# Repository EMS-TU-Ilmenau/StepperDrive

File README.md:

# StepperDrive
This embedded project features a simple controller board for a stepper motor. 
Multiple boards can be connected together. 
One of it has to be attached to USB and power supply. 
Each motor can then be controlled with simple SCPI-like commands via UART (8N1 9600baud) to move to a position, set the maximum rate and acceleration etc.

## Features
- Uses TMC2209 stepper driver IC for smooth and quiet operation
- Multiple boards can be connected to each other via ethernet-cables
- USB-C interface for control and flashing firmware

Note that there is no real anti-collision protocol, but as the communication is quit fast, there should be no problem to query each motors parameters individually with their IDs after another.
E.g. `AX1:POS?` then `AX2:POS?`.
Sending commands can be even done simultaneously, e.g. `AX1:POS 180;AX2:POS 22.5`.

## Flashing
The firmware is written in AVR-C for the ATtiny814. To start programming, an extended AVR toolchain is needed, which can be found in the Arduino IDE (the GNU AVR toolchain does NOT support the ATtiny814):
- Go to https://www.arduino.cc/en/software and scroll down to "legacy IDE (1.8.X)" and download the zipped version for your OS
- Unzip and add 
  - (Linux) *arduino-1.8.19-linux64.tar/arduino-1.8.19-linux64/arduino-1.8.19/hardware/tools/avr/bin* or 
  - (Windows) *arduino-1.8.19-windows\arduino-1.8.19\hardware\tools\avr\bin* 
  
  to your systems PATH variable (the rest of the IDE is not needed)
- Install [Make](https://www.gnu.org/software/make/#download) if you have it not already

To transfer the firmware to the microcontroller, install [pymcuprog](https://pypi.org/project/pymcuprog/).
Switch to **Prog** on the PCB.
Edit the PROGRAMMER variable (serial port) in the [firmware/Makefile](Makefile) and run `make flash clean` to build, flash and remove the built files.

## Commands
#### Common rules
Commands are simple ascii strings (no binary shenanigans, so human readable), terminated with `\n` (linefeed).
The string length must not exceed 64 chars in total (could be raised probably, not tested).
The commands have to be send with 9600 baud, 8 byte, no parity and 1 stop bit (8N1).

At the moment, only one command is parsed for each axis at a time, i.e. it is not possible to set the rate and position for a motor in one string.
However, it is possible to send one command to each motor simultaneously, by separating the commands with semicolons.
You can send commands and receive replies while the motor is moving, e.g. you can set a new position - the motor will instantly move to that position even it has not reached its last target position.

All commands must begin with `AX`, followed by the axis identifier number (default `1`) as specified with `AX1:ID <1...9>` (saved in EEPROM). 
If you forgot the ID, you can query it (works only when one controller board is connected to the hub) using `*IDN?`.

All parameters and subparameters have to be separated with a colon (`:`), followed by either a query (`?`) or the value.
E.g. `AX1:POS?`, `AX4:POW ON`, `AX2:LIM:MAX 360` or `AX3:SUB2`.
Note that the questionmark must follow immediately, while a value can have a leading white space (not required though).
When setting a parameter, it is possible to add `;*OPC?` afterwards to get feedback (`1` is returned) when the operation completed.

Commands are case-sensitive (all capital letters).

#### List of commands
- `:POW` [`ON` or `OFF`] Motor power on or off. Probably the first thing you do is to turn the power on. Default `OFF`.
- `:ACC` [positive integer] Acceleration factor. This controls how smooth the movement to a target position starts. A value of `1` is very smooth, while `100` is like constante rate. Default is `100`.
- `:DEC` [positive integer] Decceleration factor. This controls how smooth the movement to a target position ends. A value of `1` is very smooth, while `100` is like constante rate. Default is `10`.
- `:HOME` [float or integer] Moves the motor with given velocity in degree/s until the home sense pin goes low. After that, the position is defined as 0 degree. When requested, the reply is either `1` (at home) or `0` not homed/homing in progress.
- `:POS` [float or integer] Axis position (angle) in degree.
- `:LIM:MAX` [positive float or integer] Upper speed limit in degree/s. Must not be set higher than `8000*360/(substeps*steps_per_revolution)` (steps per revolution is set the in makefile and is 200 for most motors). Default 360.
- `:LIM:MIN` [positive float or integer] Lower speed limit in degree/s. Must not be set to 0. Default 10.
- `:RATE` [positive float or integer] Shorthand for `:LIM:MAX`.
- `:VEL` [positive float or integer] Rotates the axis infinitely with value in degree/s.
- `:SUB` [`8`, `16`, `32` or `64`] Number of substeps. Higher values will result in finer resolution and smoother movements, but also lower maximum rate. Default is `8`. **Important:** Set the substeps before setting or getting any parameter with degree related unit.

## TODOs
Currently, the TMC2209 is controlled via classic STEP, DIR, ENABLE, MS pins by the firmware. The hardware supports to configure the driver via its UART interface, for example to enable stall detection.

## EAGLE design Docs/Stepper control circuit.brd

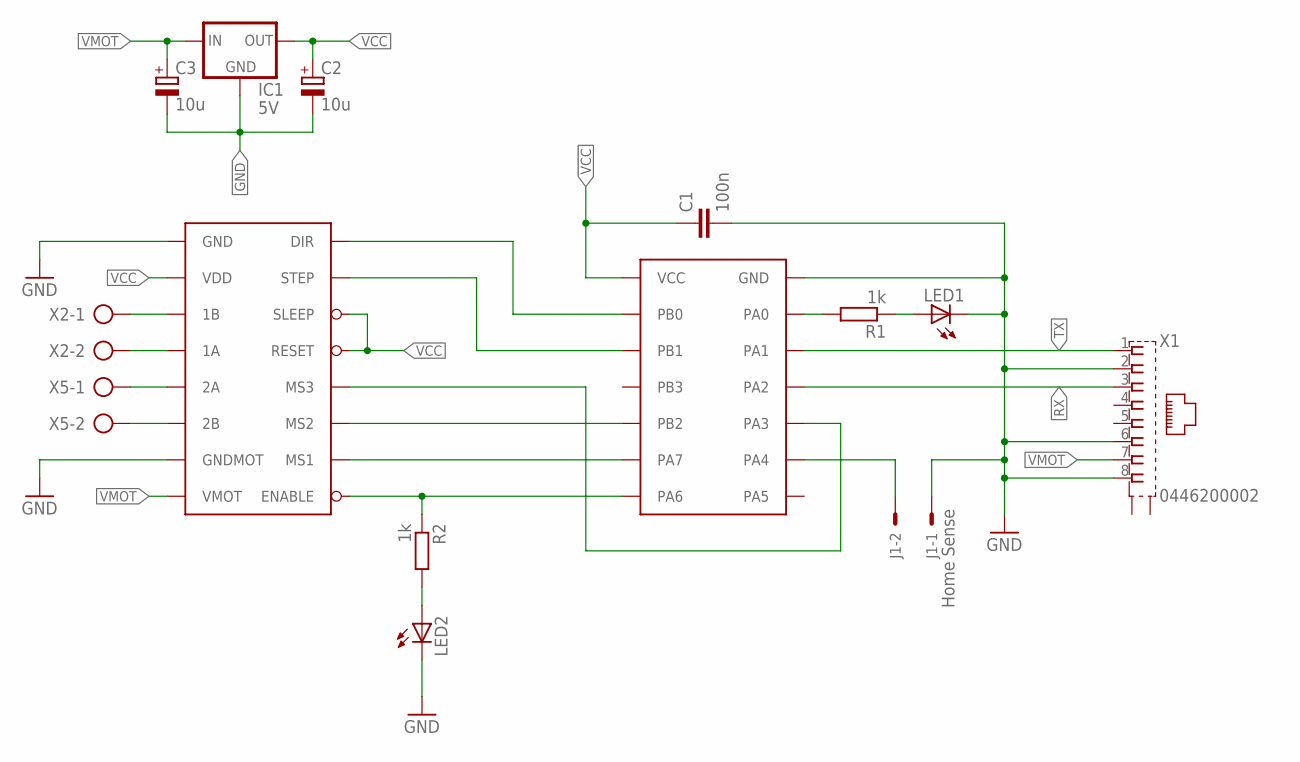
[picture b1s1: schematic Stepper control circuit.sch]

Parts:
C1: 100n; C050-025X075
C2, C3: 10u; E2,5-5
IC1: 5V; TO92-CBE
J1: Home Sense; 6410-02
LED1, LED2: LED3MM
R1, R2: 1k; 0204V
U$1: ATTINY841-BOARD; ADAPT-ATTINY841
U$2: A4988-BOARD; ADAPT-A4988
X1: 0446200002
X2, X5: AK500/2

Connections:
DIR: U$1.PB0, U$2.DIR
ENABLE: R2.1, U$1.PA6, U$2.ENABLE
GND: C1.2, C2.-, C3.-, IC1.B (GND), J1.1, LED1.K (C), LED2.K (C), U$1.GND, U$2.GND, U$2.GNDMOT, X1.2, X1.6, X1.8
MS1: U$1.PA7, U$2.MS1
MS2: U$1.PB2, U$2.MS2
MS3: U$1.PA3, U$2.MS3
unnamed: J1.2, U$1.PA4
unnamed: LED2.A, R2.2
unnamed: U$2.2B, X5.2
unnamed: U$2.2A, X5.1
unnamed: U$2.1A, X2.2
unnamed: R1.2, U$1.PA0
unnamed: LED1.A, R1.1
unnamed: U$2.1B, X2.1
RX: U$1.PA2, X1.3
STEP: U$1.PB1, U$2.STEP
TX: U$1.PA1, X1.1
VCC: C1.1, C2.+, IC1.C (OUT), U$1.VCC, U$2.RESET, U$2.SLEEP, U$2.VDD
VMOT: C3.+, IC1.E (IN), U$2.VMOT, X1.7

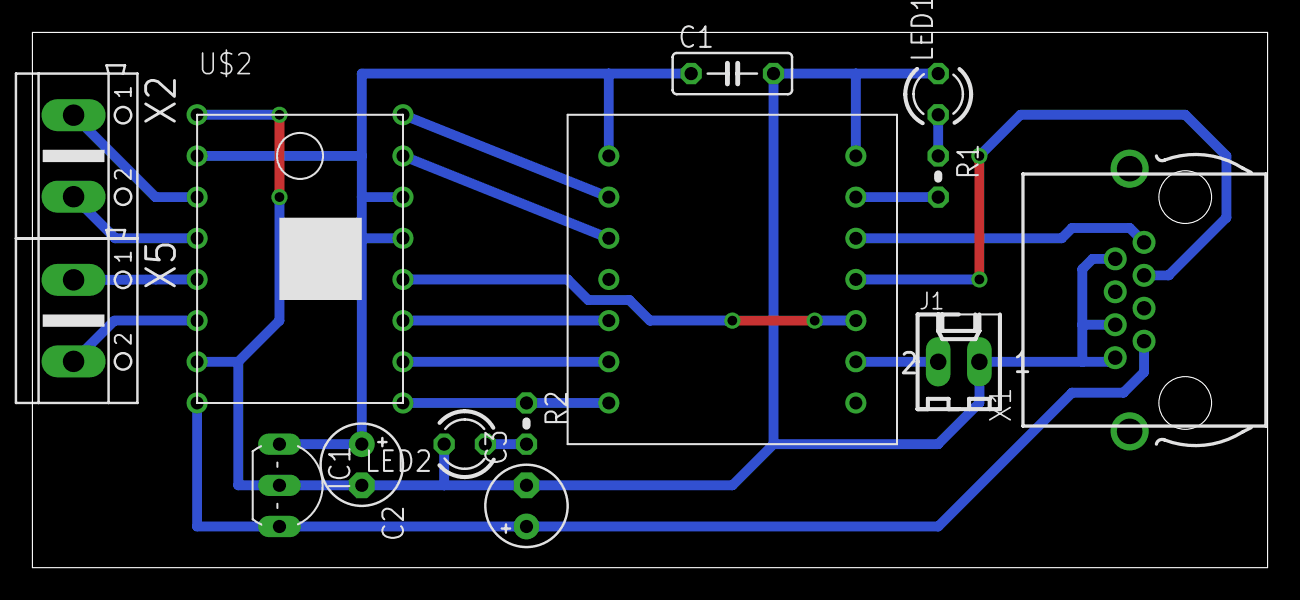
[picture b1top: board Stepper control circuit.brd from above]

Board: 2 copper layers, 76.2 x 33.0 mm, 14 parts (0 on the bottom side), 19 nets.

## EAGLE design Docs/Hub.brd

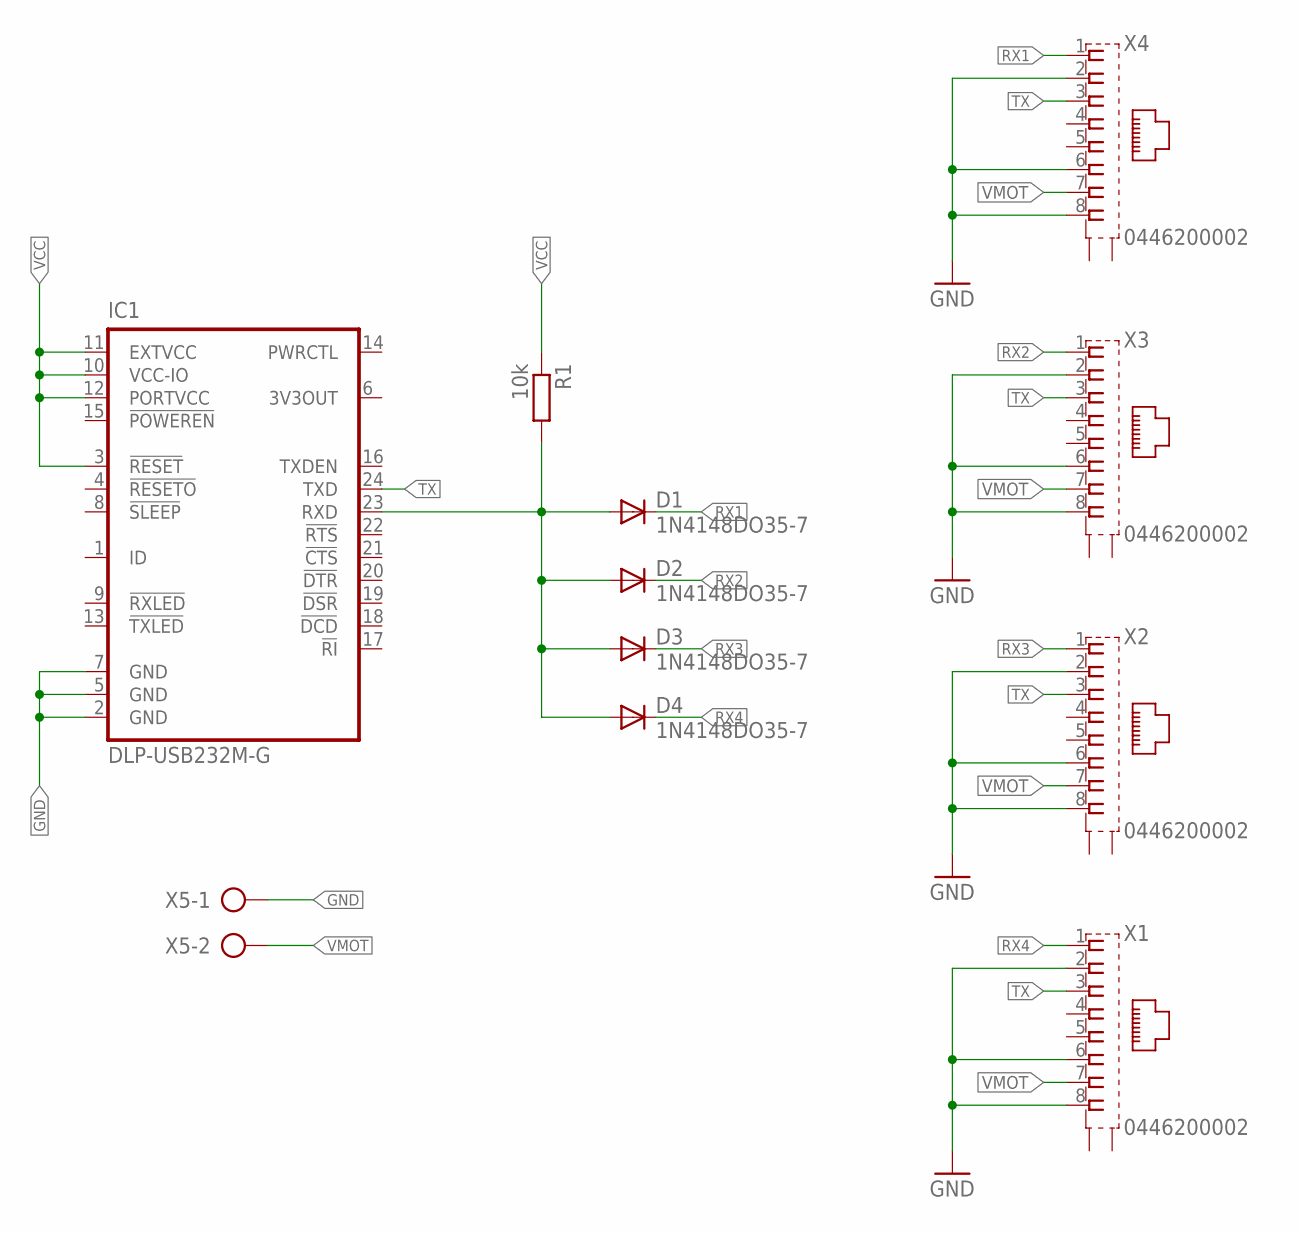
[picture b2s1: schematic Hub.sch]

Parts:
D1, D2, D3, D4: 1N4148DO35-7; DO35-7
IC1: DLP-USB232M-G; DLP-USB232M
R1: 10k; 0204/7
X1, X2, X3, X4: 0446200002
X5: AK500/2

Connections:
GND: IC1.2 (GND), IC1.5 (GND), IC1.7 (GND), X1.2, X1.6, X1.8, X2.2, X2.6, X2.8, X3.2, X3.6, X3.8, X4.2, X4.6, X4.8, X5.1
unnamed: D1.A, D2.A, D3.A, D4.A, IC1.23 (RXD), R1.2
RX1: D1.C, X4.1
RX2: D2.C, X3.1
RX3: D3.C, X2.1
RX4: D4.C, X1.1
TX: IC1.24 (TXD), X1.3, X2.3, X3.3, X4.3
VCC: IC1.3 (!RESET), IC1.10 (VCC-IO), IC1.11 (EXTVCC), IC1.12 (PORTVCC), R1.1
VMOT: X1.7, X2.7, X3.7, X4.7, X5.2

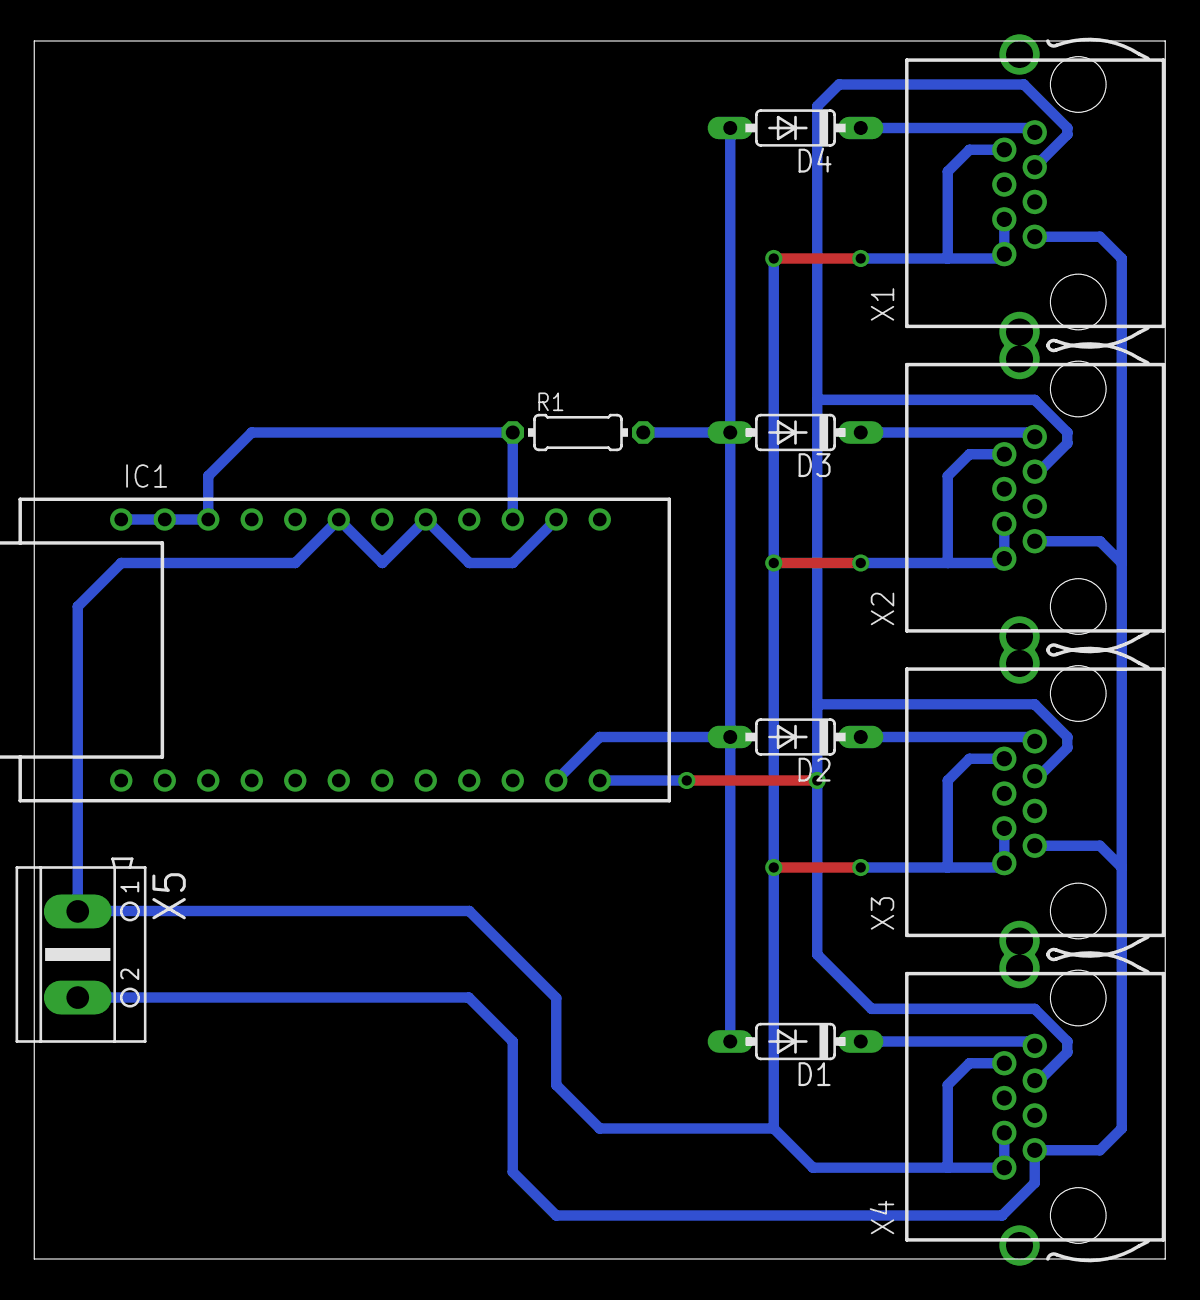
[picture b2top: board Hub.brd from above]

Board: 2 copper layers, 66.0 x 71.1 mm, 11 parts (0 on the bottom side), 9 nets.

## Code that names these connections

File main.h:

#include <avr/io.h> // for pin definitions
#include <stdint.h> // for data types

// define macros and constants
#define STR_HELPER(x) #x
#define STR(x) STR_HELPER(x)
#define TRUE 1
#define FALSE 0
#define HOME_OFF 0 // homing states
#define HOME_SEARCH 1
#define HOME_FOUND 2
#define HOME_ON 3
#define UART_BAUD 9600UL
#define UART_UBRR (F_CPU/(8*UART_BAUD)-1) // calculate register value for baudrate for U2Xn = 1
#define UART_MAXSTRLEN 64
#define STR_TERM '\n'
#define RADIX 10 // for itoa
#define F_TINT 8000 // timer interrupt frequency
#define C_PRESC 64 // control frequency that much slower than F_TINT
#define CMD_ID "AX" STR(AX_ID) // axis specific commands must start with AX<id>
#define PIN_ENABLE PA6 // motor enable pin (low active)
#define PIN_STEP PB1 // motor step pin
#define PIN_DIR PB0 // motor direction pin
#define PIN_LED PA0 // status or testing LED pin
#define PIN_HOME PA4 // homing switch pin (low active)
#define PIN_SS1 PA7 // substep bit 1
#define PIN_SS2 PB2 // substep bit 2
#define PIN_SS3 PA3 // substep bit 3

// structs
typedef struct {
	// for a P control loop
	int32_t tarStepPos;
	int32_t curStepPos;
	int32_t oldStepPos;
	uint16_t tic;
	uint16_t stepPeriod;
	int8_t tarDir;
} pCtrl_t;

// variables
char uartReceiveStr[UART_MAXSTRLEN] = "";
char uartSendStr[UART_MAXSTRLEN] = "";
uint8_t gotCommand = FALSE;
volatile uint8_t gotControlReq = FALSE;
uint8_t substeps = 4; // num of microsteps which make 1 full step
uint16_t maxStepRate, minStepRate; // step rate limits
uint16_t kAcc = 100; // acceleration proportion
uint16_t kDec= 10; // decceleration proportion
uint8_t homing = HOME_OFF; // homing state
pCtrl_t ctrlState;

// prototypes
void GPIO_Init();
void USART0_Init();
void USART0_ReceiveChar();
void USART0_SendChar(const char c);
void USART0_SendString(const char* strP);
void ParseCommand(const char* strP);
void Timer0_Init();
int32_t DegToSteps(int32_t deg);
int32_t StepsToDeg(int32_t steps);
void SendNum(int16_t num);
void Control(pCtrl_t* ctrlP);
void PhyStep(pCtrl_t* ctrlP);
void SetSubsteps(uint8_t ss);
int32_t DegStrToSteps(const char* strP);
void SendStepsAsDeg(int32_t steps);

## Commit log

2017-10-18 Added notes why the ugly PCB
2017-10-18 Inverted PCB images to make it more printer friendly
2017-10-18 Try to make schematic and PCB images appear next to each other
2017-12-05 Fixed bug that caused to ignore the first received message from the host. Requesting the IDN now only returns the actual axis identifier.
2017-12-05 The first message from the host is still ignored because of hardware reasons (serial port produces random bytes when plugged), so reverted the fix
2019-09-02 Added rate parameter as shorthand for LIM:MAX for compatibility to old pcb
2019-09-03 Removed author. Added more infos about flashing
2020-05-28 Fixed setting 16 substeps
2020-05-29 added acceleration. Replaced KP by ACC and DEC factors
2020-07-01 replaced sendNum by correct parsing functions for each parameter
2020-07-01 to reduce interrupts, USART chars are now received in main loop. String termination is now only linefeed
2020-07-01 updated documentation about the string termination change to linefeed only
2024-05-16 added *OPC? command
2024-05-16 all new board with TMC2209 driver and without the need of an hub.
2024-05-17 fixed potential problem when reading or writing the axis ID
2024-05-17 added GND Via for stall LED
2024-05-17 minor fixes for potential problems
2024-05-22 removed repeated eeprom read as there seems no effect. Fixed float parsing
2024-05-22 fixed float parsing
